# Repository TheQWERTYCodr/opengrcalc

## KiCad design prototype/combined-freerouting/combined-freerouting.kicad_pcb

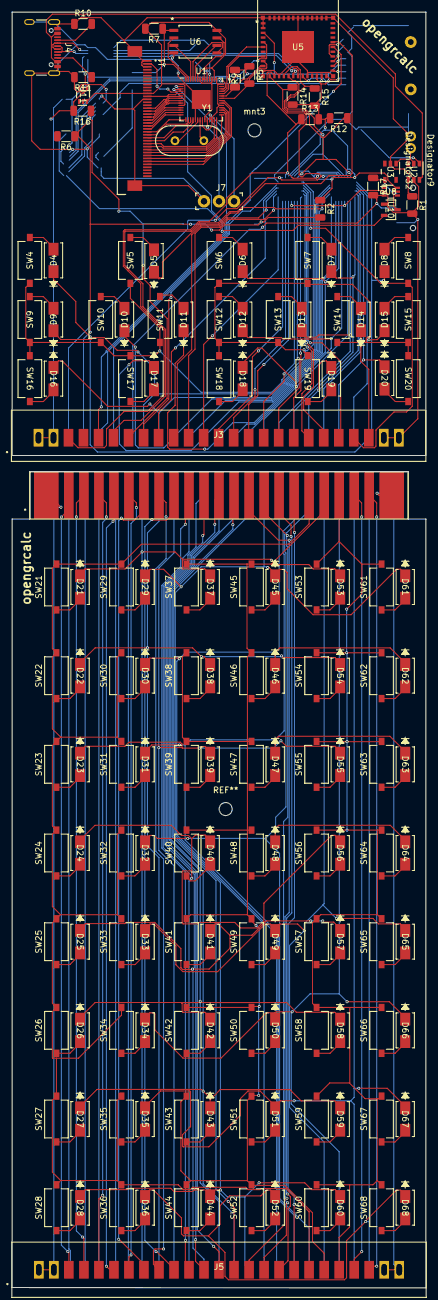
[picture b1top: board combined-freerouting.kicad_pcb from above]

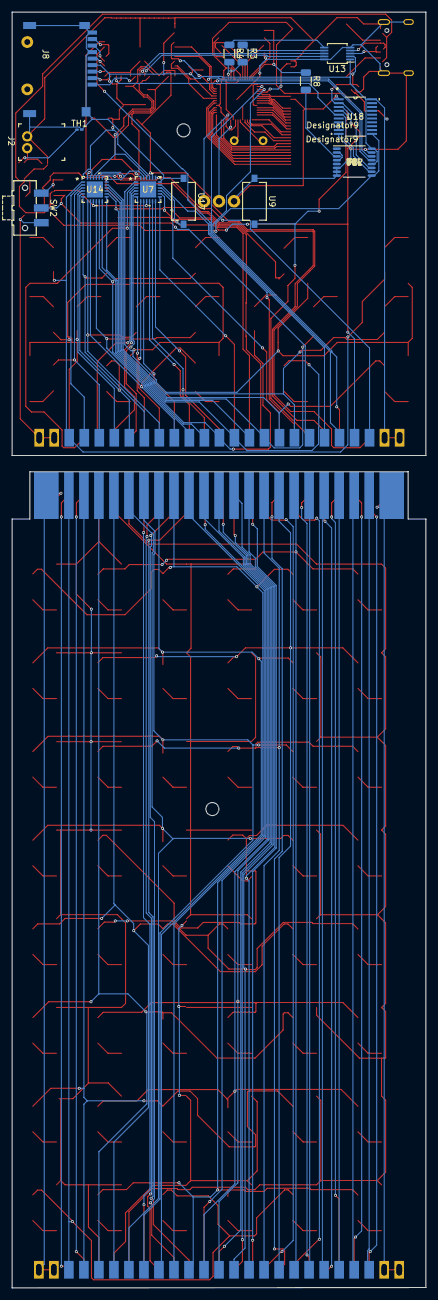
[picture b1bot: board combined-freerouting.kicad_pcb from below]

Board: 2 copper layers, 70.0 x 215.8 mm, 174 parts (14 on the bottom side), 219 nets.

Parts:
D4, D5, D6, D7, D8, D9, D10, D11, D12, D13, D14, D15, D16, D17, D18, D19, D20: D_Small; SMA_SDS
D21, D22, D23, D24, D25, D26, D27, D28, D29, D30, D31, D32, D33, D34, D35, D36, D37, D38, D39, D40, D41, D42, D43, D44, D45, D46, D47, D48, D49, D50, D51, D52, D53, D54, D55, D56, D57, D58, D59, D60, D61, D62, D63, D64, D65, D66, D67, D68: SMA_SDS
J1: FFC2B21-40-T_REVA; GCT_FFC2B21-40-T_REVA
J2: battery; PinHeader_1x2_P2mm_Drill1mm_RA
J3, J5: 5530843-5; edgeport
J4: USB4105-GF-A; USB_C_Receptacle_GCT_USB4105-xx-A_16P_TopMnt_Horizontal
J7: 640456-3; PinHeader_1x3_P2.54_Drill1.1mm
J8: Micro_SD_Card; msd-11-a
R1: 1K; R_1206_3216Metric
R2, R5, R6, R7, R9, R16, R17: 10k; R_1206_3216Metric
R3, R4: 27; R_1206_3216Metric
R8: 1k; R_1206_3216Metric
R10, R11: 5.1k; R_1206_3216Metric
R12, R13, R14, R15: 2k; R_1206_3216Metric
SW2: PWR_SWITCH; SW_SPDT_CK-JS102011SAQN
SW4: KP_CTRL; SW_Tactile_SPST_NO_Straight_CK_PTS636Sx25SMTRLFS
SW5: KP_SHIFT; SW_Tactile_SPST_NO_Straight_CK_PTS636Sx25SMTRLFS
SW6: KP_UP; SW_Tactile_SPST_NO_Straight_CK_PTS636Sx25SMTRLFS
SW7: KP_HOME; SW_Tactile_SPST_NO_Straight_CK_PTS636Sx25SMTRLFS
SW8: KP_POWER; SW_Tactile_SPST_NO_Straight_CK_PTS636Sx25SMTRLFS
SW9: KP_ALT; SW_Tactile_SPST_NO_Straight_CK_PTS636Sx25SMTRLFS
SW10: KP_MODLOCK; SW_Tactile_SPST_NO_Straight_CK_PTS636Sx25SMTRLFS
SW11: KP_LEFT; SW_Tactile_SPST_NO_Straight_CK_PTS636Sx25SMTRLFS
SW12: KP_OK; SW_Tactile_SPST_NO_Straight_CK_PTS636Sx25SMTRLFS
SW13: KP_RIGHT; SW_Tactile_SPST_NO_Straight_CK_PTS636Sx25SMTRLFS
SW14: KP_HELP; SW_Tactile_SPST_NO_Straight_CK_PTS636Sx25SMTRLFS
SW15: KP_PROG; SW_Tactile_SPST_NO_Straight_CK_PTS636Sx25SMTRLFS
SW16: KP_MENU; SW_Tactile_SPST_NO_Straight_CK_PTS636Sx25SMTRLFS
SW17: KP_BACK; SW_Tactile_SPST_NO_Straight_CK_PTS636Sx25SMTRLFS
SW18: KP_DOWN; SW_Tactile_SPST_NO_Straight_CK_PTS636Sx25SMTRLFS
SW19: KP_TASKS; SW_Tactile_SPST_NO_Straight_CK_PTS636Sx25SMTRLFS
SW20: KP_FUNCS; SW_Tactile_SPST_NO_Straight_CK_PTS636Sx25SMTRLFS
SW21, SW22, SW23, SW24, SW25, SW26, SW27, SW28, SW29, SW30, SW31, SW32, SW33, SW34, SW35, SW36, SW37, SW38, SW39, SW40, SW41, SW42, SW43, SW44, SW45, SW46, SW47, SW48, SW49, SW50, SW51, SW52, SW53, SW54, SW55, SW56, SW57, SW58, SW59, SW60, SW61, SW62, SW63, SW64, SW65, SW66, SW67, SW68: SW_Tactile_SPST_NO_Straight_CK_PTS636Sx25SMTRLFS
TH1: battery thermistor; R_0201_0603Metric_Pad0.64x0.40mm_HandSolder
U1: RP2040; QFN-56-1EP_7x7mm_P0.4mm_EP3.2x3.2mm
U2: BQ21040DBVR; DBV0006A_N
U3: TPS613221ADBVR; DBV0005A_N
U4: edge
U5: ESP32-C6-MINI-1-H4; ESP32-C6_EXP
U6: W25Q32JVSSIQ; SOIC-8_5P28X5P28_WIN
U7, U14: KTS1622EUAA-TR; TQFN44-24_KIN
U8, U11: TPS22919DCKR; DCK0006A_N
U9: FLASH_BTN; SW_Tactile_SPST_NO_Straight_CK_PTS636Sx25SMTRLFS
U10: SOT-23_M3_MCH
U12: CD4053B; PW0016A_N
U13: FSUSB42MUX; MSOP-10_3x3mm_P0.5mm
U17: MODE_BTN; SW_Tactile_SPST_NO_Straight_CK_PTS636Sx25SMTRLFS
U18: SN74HCT373PWR; PW20
Y1: 12MHz; Crystal_HC49-4H_Vertical
mnt3: MountingHole_2.2mm_M2

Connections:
+3.3V: J3.1, J3.2, J3.3, J3.4, J8.4 (VDD), R2.1, R5.1, R9.1, R12.2, R13.2, R14.2, R15.2, R16.2, U5.3 (3V3), U5.22 (IO8), U7.21 (VDD_P), U7.23 (VDD_I2C), U8.6 (OUT), U10.3 (V_{CC}), U11.1 (IN), U12.12 (A0), U12.16 (VDD), U13.1 (VCC), U14.18 (ADDR), U14.21 (VDD_P), U14.23 (VDD_I2C), U18.20 (VCC)
/64_GPIO_I2C/~INT: R15.1, U5.15 (IO6), U7.22 (*INT), U14.22 (*INT)
/64_GPIO_I2C/~RESET: R12.1, U5.16 (IO7), U7.24 (*RESET), U14.24 (*RESET)
/CHIP_EN: U5.8 (EN), U12.14 (A)
/DISP_CONN/CS: J1.36, U1.35 (GPIO23)
/DISP_CONN/DB0: J1.32, U1.30 (GPIO19)
/DISP_CONN/DB1: J1.31, U1.29 (GPIO18)
/DISP_CONN/DB2: J1.30, U1.28 (GPIO17)
/DISP_CONN/DB3: J1.29, U1.27 (GPIO16)
/DISP_CONN/DB4: J1.28, U1.18 (GPIO15)
/DISP_CONN/DB5: J1.27, U1.17 (GPIO14)
/DISP_CONN/DB6: J1.26, U1.16 (GPIO13)
/DISP_CONN/DB7: J1.25, U1.15 (GPIO12)
/DISP_CONN/DB8: J1.24, U1.14 (GPIO11)
/DISP_CONN/DB9: J1.23, U1.13 (GPIO10)
/DISP_CONN/DB10: J1.22, U1.12 (GPIO9)
/DISP_CONN/DB11: J1.21, U1.11 (GPIO8)
/DISP_CONN/DB12: J1.20, U1.9 (GPIO7)
/DISP_CONN/DB13: J1.19, U1.8 (GPIO6)
/DISP_CONN/DB14: J1.18, U1.7 (GPIO5)
/DISP_CONN/DB15: J1.17, U1.6 (GPIO4)
/DISP_CONN/LEDA: J1.2, U1.4 (GPIO2)
/DISP_CONN/RD: J1.33, U1.31 (GPIO20)
/DISP_CONN/RESET: J1.13, U1.5 (GPIO3)
/DISP_CONN/RS (D/C): J1.35, U1.34 (GPIO22)
/DISP_CONN/WR: J1.34, U1.32 (GPIO21)
/ESP32/D+: U5.18 (IO13), U13.9 (HSD2+)
/ESP32/D-: U5.17 (IO12), U13.8 (HSD2-)
/ESP32/IO_14: J8.1 (DAT2), U5.19 (IO14)
/ESP32/IO_18: J8.2 (DAT3/CD), U5.24 (IO18)
/ESP32/IO_19: J8.3 (CMD), U5.25 (IO19)
/ESP32/IO_20: J8.5 (CLK), U5.26 (IO20)
/ESP32/IO_21: J8.7 (DAT0), U5.27 (IO21)
/ESP32/IO_22: J8.8 (DAT1), U5.28 (IO22)
/ESP32/LP_UART_CTSN: U1.39 (GPIO27_ADC1), U5.6 (IO3)
/ESP32/LP_UART_RTSN: U1.38 (GPIO26_ADC0), U5.5 (IO2)
/ESP32/LP_UART_RXD: R5.2, U1.36 (GPIO24), U5.9 (IO4)
/ESP32/LP_UART_TXD: R9.2, U1.37 (GPIO25), U5.10 (IO5)
/ESP32_UART0_RX: J3.11, U5.30 (RXD0)
/ESP32_UART0_TX: J3.12, U5.31 (TXD0)
/FLASH_LATCH: U5.23 (IO9), U12.10 (S2), U18.5 (2Q)
/FLASH_PIN: J3.14, R16.1, U9.2, U18.4 (2D)
/GLOBAL_RESET_PIN: J3.13, R17.2, SW2.2 (B), U8.3 (ON)
/GPIO_I2C_SCL: J3.5, R14.1, U5.12 (IO0), U7.19 (SCL), U14.19 (SCL)
/GPIO_I2C_SDA: J3.6, R13.1, U5.13 (IO2), U7.20 (SDA), U14.20 (SDA)
/KPA0: J3.46, SW4.1, SW5.1, SW6.1, SW7.1, SW9.1, SW10.1, SW11.1, SW12.1, SW13.1, SW14.1, SW15.1, SW16.1, SW17.1, SW18.1, SW19.1, SW20.1, U7.1 (P0_0)
/KPA1: J3.44, SW8.1, U7.2 (P0_1)
/KPA2: J3.42, U7.3 (P0_2)
/KPA3: J3.40, U7.4 (P0_3)
/KPA4: J3.38, U7.5 (P0_4)
/KPA5: J3.36, U7.6 (P0_5)
/KPA6: J3.34, U7.7 (P0_6)
/KPA7: J3.32, U7.8 (P0_7)
/KPA8: J3.30, U7.10 (P1_0)
/KPA9: J3.28, U7.11 (P1_1)
/KPA10: J3.26, U7.12 (P1_2)
/KPA11: J3.24, U7.13 (P1_3)
/KPA12: J3.22, U7.14 (P1_4)
/KPA13: J3.20, U7.15 (P1_5)
/KPA14: J3.18, U7.16 (P1_6)
/KPA15: J3.16, U7.17 (P1_7)
/KPB0: D4.1 (K), D8.1 (K), J3.45, U14.1 (P0_0)
/KPB1: D15.1 (K), J3.43, U14.2 (P0_1)
/KPB2: D20.1 (K), J3.41, U14.3 (P0_2)
/KPB3: D14.1 (K), J3.39, U14.4 (P0_3)
/KPB4: D19.1 (K), J3.37, U14.5 (P0_4)
/KPB5: D7.1 (K), J3.35, U14.6 (P0_5)
/KPB6: D13.1 (K), J3.33, U14.7 (P0_6)
/KPB7: D18.1 (K), J3.31, U14.8 (P0_7)
/KPB8: D12.1 (K), J3.29, U14.10 (P1_0)
/KPB9: D6.1 (K), J3.27, U14.11 (P1_1)
/KPB10: D11.1 (K), J3.25, U14.12 (P1_2)
/KPB11: D17.1 (K), J3.23, U14.13 (P1_3)
/KPB12: D5.1 (K), J3.21, U14.14 (P1_4)
/KPB13: D10.1 (K), J3.19, U14.15 (P1_5)
/KPB14: D16.1 (K), J3.17, U14.16 (P1_6)
/KPB15: D9.1 (K), J3.15, U14.17 (P1_7)
/LATCH_PULSE: U10.2 (RESET), U12.9 (S3), U18.11 (LE)
/MODE_MUX/D+: J4.A6 (DP1), J4.B6 (DP2), U13.3 (D+)
/MODE_MUX/D+ Y: R3.1, U13.7 (HSD1+)
/MODE_MUX/D-: J4.A7 (DN1), J4.B7 (DN2), U13.4 (D-)
/MODE_MUX/D- Y: R4.1, U13.6 (HSD1-)
/MODE_PIN: J3.7, R2.2, R6.1, U17.2, U18.3 (1D)
/PWR_RP2040: J1.12, R7.2, U1.1 (IOVDD), U1.10 (IOVDD), U1.22 (IOVDD), U1.26 (RUN), U1.33 (IOVDD), U1.42 (IOVDD), U1.43 (ADC_AVDD), U1.44 (VREG_IN), U1.48 (USB_VDD), U1.49 (IOVDD), U6.8 (VCC), U11.6 (OUT)
/RP2040_BOOTPIN: R8.2, U12.3 (C1)
/RP2040_CHIP_EN_OUT: U1.40 (GPIO28_ADC2), U12.13 (A1)
/RP2040_UART0_RX: J3.10, U1.3 (GPIO1)
/RP2040_UART0_TX: J3.9, U1.2 (GPIO0)
/RUN_MODE: U11.3 (ON), U12.11 (S1), U13.2 (SEL), U18.2 (1Q)
/mathboard/3v3: J5.1, J5.2, J5.3, J5.4, U4.1 (3V3), U4.2 (3V3)
/mathboard/a0: J5.46, U4.46 (KPA0)
/mathboard/a1: J5.44, U4.44 (KPA1)
/mathboard/a2: J5.42, SW53.2, SW54.2, SW55.2, SW56.2, SW57.2, SW58.2, SW59.2, SW60.2, SW61.2, SW62.2, SW63.2, SW64.2, SW65.2, SW66.2, SW67.2, SW68.2, U4.42 (KPA2)
/mathboard/a3: J5.40, SW37.2, SW38.2, SW39.2, SW40.2, SW41.2, SW42.2, SW43.2, SW44.2, SW45.2, SW46.2, SW47.2, SW48.2, SW49.2, SW50.2, SW51.2, SW52.2, U4.40 (KPA3)
/mathboard/a4: J5.38, SW21.2, SW22.2, SW23.2, SW24.2, SW25.2, SW26.2, SW27.2, SW28.2, SW29.2, SW30.2, SW31.2, SW32.2, SW33.2, SW34.2, SW35.2, SW36.2, U4.38 (KPA4)
/mathboard/a5: J5.36, U4.36 (KPA5)
/mathboard/a6: J5.34, U4.34 (KPA6)
/mathboard/a7: J5.32, U4.32 (KPA7)
/mathboard/a8: J5.30, U4.30 (KPA8)
/mathboard/a9: J5.28, U4.28 (KPA9)
/mathboard/a10: J5.26, U4.26 (KPA10)
/mathboard/a11: J5.24, U4.24 (KPA11)
/mathboard/a12: J5.22, U4.22 (KPA12)
/mathboard/a13: J5.20, U4.20 (KPA13)
/mathboard/a14: J5.18, U4.18 (KPA14)
/mathboard/a15: J5.16, U4.16 (KPA15)
/mathboard/b0: D36.1 (K), D52.1 (K), D68.1 (K), J5.45, U4.45 (KPB0)
/mathboard/b1: D35.1 (K), D51.1 (K), D67.1 (K), J5.43, U4.43 (KPB1)
/mathboard/b2: D34.1 (K), D50.1 (K), D66.1 (K), J5.41, U4.41 (KPB2)
/mathboard/b3: D33.1 (K), D49.1 (K), D65.1 (K), J5.39, U4.39 (KPB3)
/mathboard/b4: D32.1 (K), D48.1 (K), D64.1 (K), J5.37, U4.37 (KPB4)
/mathboard/b5: D31.1 (K), D47.1 (K), D63.1 (K), J5.35, U4.35 (KPB5)
/mathboard/b6: D30.1 (K), D46.1 (K), D62.1 (K), J5.33, U4.33 (KPB6)
/mathboard/b7: D29.1 (K), D45.1 (K), D61.1 (K), J5.31, U4.31 (KPB7)
/mathboard/b8: D28.1 (K), D44.1 (K), D60.1 (K), J5.29, U4.29 (KPB8)
/mathboard/b9: D27.1 (K), D43.1 (K), D59.1 (K), J5.27, U4.27 (KPB9)
/mathboard/b10: D26.1 (K), D42.1 (K), D58.1 (K), J5.25, U4.25 (KPB10)
/mathboard/b11: D25.1 (K), D41.1 (K), D57.1 (K), J5.23, U4.23 (KPB11)
/mathboard/b12: D24.1 (K), D40.1 (K), D56.1 (K), J5.21, U4.21 (KPB12)
/mathboard/b13: D23.1 (K), D39.1 (K), D55.1 (K), J5.19, U4.19 (KPB13)
/mathboard/b14: D22.1 (K), D38.1 (K), D54.1 (K), J5.17, U4.17 (KPB14)
/mathboard/b15: D21.1 (K), D37.1 (K), D53.1 (K), J5.15, U4.15 (KPB15)
/mathboard/esp_rx: J5.11, U4.11 (ESP32_RX)
/mathboard/esp_tx: J5.12, U4.12 (ESP32_TX)
/mathboard/flash: J5.14, U4.14 (FLASH_PIN)
/mathboard/int: J5.8, U4.8 (~INT)
/mathboard/mode: J5.7, U4.7 (MODE_PIN)
/mathboard/reset: J5.13, U4.13 (GLOBAL_RESET_PIN)
/mathboard/rp_rx: J5.10, U4.10 (RP2040_RX)
/mathboard/rp_tx: J5.9, U4.9 (RP2040_TX)
/mathboard/scl: J5.5, U4.5 (SCL)
/mathboard/sda: J5.6, U4.6 (SDA)
GND: J1.1, J1.3, J1.14, J1.S1 (SHIELD), J1.S2 (SHIELD__1), J2.2, J3.47, J3.48, J3.49, J3.50, J4.A1 (GND), J4.B1 (GND), J4.S1 (Shield), J5.47, J5.48, J5.49, J5.50, J7.1, J8.6 (VSS), J8.9 (SHIELD), R1.2, R10.1, R11.2, SW2.3 (C), TH1.2, U1.19 (TESTEN), U1.57 (GND), U2.5 (VSS), U3.2 (GND), U4.49 (GND), U4.50 (GND), U5.1 (GND), U5.2 (GND), U5.11 (GND), U5.14 (GND), U5.20 (IO15), U5.36 (GND), U5.37 (GND), U5.38 (GND), U5.39 (GND), U5.40 (GND), U5.41 (GND), U5.42 (GND), U5.43 (GND), U5.44 (GND), U5.45 (GND), U5.46 (GND), U5.47 (GND), U5.48 (GND), U5.49 (GND), U5.50 (GND), U5.51 (GND), U5.52 (GND), U5.53 (GND), U6.4 (GND), U7.9 (VSS), U7.18 (ADDR), U8.2 (GND), U9.1, U10.1 (GND), U11.2 (GND), U12.6 (INH), U12.7 (VEE), U12.8 (VSS), U12.15 (B), U13.5 (GND), U13.10 (~OE), U14.9 (VSS), U17.1, U18.1 (*OE), U18.10 (GND)
unnamed: D4.2 (A), SW4.2
unnamed: D5.2 (A), SW5.2
unnamed: D6.2 (A), SW6.2
unnamed: D7.2 (A), SW7.2
unnamed: D8.2 (A), SW8.2
unnamed: D9.2 (A), SW9.2
unnamed: D10.2 (A), SW10.2
unnamed: D11.2 (A), SW11.2
unnamed: D12.2 (A), SW12.2
unnamed: D13.2 (A), SW13.2
unnamed: D14.2 (A), SW14.2
unnamed: D15.2 (A), SW15.2
unnamed: D16.2 (A), SW16.2
unnamed: D17.2 (A), SW17.2
unnamed: D18.2 (A), SW18.2
unnamed: D19.2 (A), SW19.2
unnamed: D20.2 (A), SW20.2
unnamed: D21.2 (A), SW21.1
unnamed: D22.2 (A), SW22.1
unnamed: D23.2 (A), SW23.1
unnamed: D24.2 (A), SW24.1
unnamed: D25.2 (A), SW25.1
unnamed: D26.2 (A), SW26.1
unnamed: D27.2 (A), SW27.1
unnamed: D28.2 (A), SW28.1
unnamed: D29.2 (A), SW29.1
unnamed: D30.2 (A), SW30.1
unnamed: D31.2 (A), SW31.1
unnamed: D32.2 (A), SW32.1
unnamed: D33.2 (A), SW33.1
unnamed: D34.2 (A), SW34.1
unnamed: D35.2 (A), SW35.1
unnamed: D36.2 (A), SW36.1
unnamed: D37.2 (A), SW37.1
unnamed: D38.2 (A), SW38.1
unnamed: D39.2 (A), SW39.1
unnamed: D40.2 (A), SW40.1
unnamed: D41.2 (A), SW41.1
unnamed: D42.2 (A), SW42.1
unnamed: D43.2 (A), SW43.1
unnamed: D44.2 (A), SW44.1
unnamed: D45.2 (A), SW45.1
unnamed: D46.2 (A), SW46.1
unnamed: D47.2 (A), SW47.1
unnamed: D48.2 (A), SW48.1
unnamed: D49.2 (A), SW49.1
unnamed: D50.2 (A), SW50.1
unnamed: D51.2 (A), SW51.1
unnamed: D52.2 (A), SW52.1
unnamed: D53.2 (A), SW53.1
unnamed: D54.2 (A), SW54.1
unnamed: D55.2 (A), SW55.1
unnamed: D56.2 (A), SW56.1
unnamed: D57.2 (A), SW57.1
unnamed: D58.2 (A), SW58.1
unnamed: D59.2 (A), SW59.1
unnamed: D60.2 (A), SW60.1
unnamed: D61.2 (A), SW61.1
unnamed: D62.2 (A), SW62.1
unnamed: D63.2 (A), SW63.1
unnamed: D64.2 (A), SW64.1
unnamed: D65.2 (A), SW65.1
unnamed: D66.2 (A), SW66.1
unnamed: D67.2 (A), SW67.1
unnamed: D68.2 (A), SW68.1
unnamed: J4.A5 (CC1), R10.2
unnamed: J4.B5 (CC2), R11.1
unnamed: U1.52 (QSPI_SCLK), U6.6 (CLK)
unnamed: U1.53 (QSPI_SD0), U6.5 (DI(IO0))
unnamed: U1.55 (QSPI_SD1), U6.2 (DO(IO1))
unnamed: U1.54 (QSPI_SD2), U6.3 (/WP(IO2))
unnamed: U1.51 (QSPI_SD3), U6.7 (/HOLD_OR_/RESET(IO3))
unnamed: R7.1, R8.1, U1.56 (QSPI_SS), U6.1 (/CS)
unnamed: J7.2, U1.24 (SWCLK)
unnamed: J7.3, U1.25 (SWD)
unnamed: R4.2, U1.46 (USB_DM)
unnamed: R3.2, U1.47 (USB_DP)
unnamed: U1.23 (DVDD), U1.45 (VREG_VOUT), U1.50 (DVDD)
unnamed: U1.20 (XIN), Y1.1
unnamed: U1.21 (XOUT), Y1.2
unnamed: R1.1, U2.4 (ISET)
unnamed: J2.1, U2.2 (OUT), U3.1 (SW)
unnamed: TH1.1, U2.1 (TS)
unnamed: U12.2 (B0), U12.4 (C)
VBUS: J4.A4 (VBUS), J4.B4 (VBUS), U2.6 (IN)
VCC: R17.1, SW2.1 (A), U3.4 (VOUT), U8.1 (IN)

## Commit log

2024-02-20 updated pcb & pricing data
2024-02-27 finished calculator & mathboard PCBs, updated pricing calc
2024-02-27 clarify writing in protocol.cpp
2024-02-27 updated pricing calc
2024-02-27 add pricing db lock file to .gitignore
2024-02-28 added support for constant prices, taxes, and fixed bulk quantities to the pricing calculator; fixed error in the PCB's edge cuts
2024-03-02 minor modification to pricing calc (switch to fixed-width integer types)
2024-03-02 updated copyright notice on pricing-calc.cpp
2024-03-07 added copyright notices and license file
2024-03-31 transition opengrcalc to be a package running on the openmini api
2024-03-31 remove old gitignore
